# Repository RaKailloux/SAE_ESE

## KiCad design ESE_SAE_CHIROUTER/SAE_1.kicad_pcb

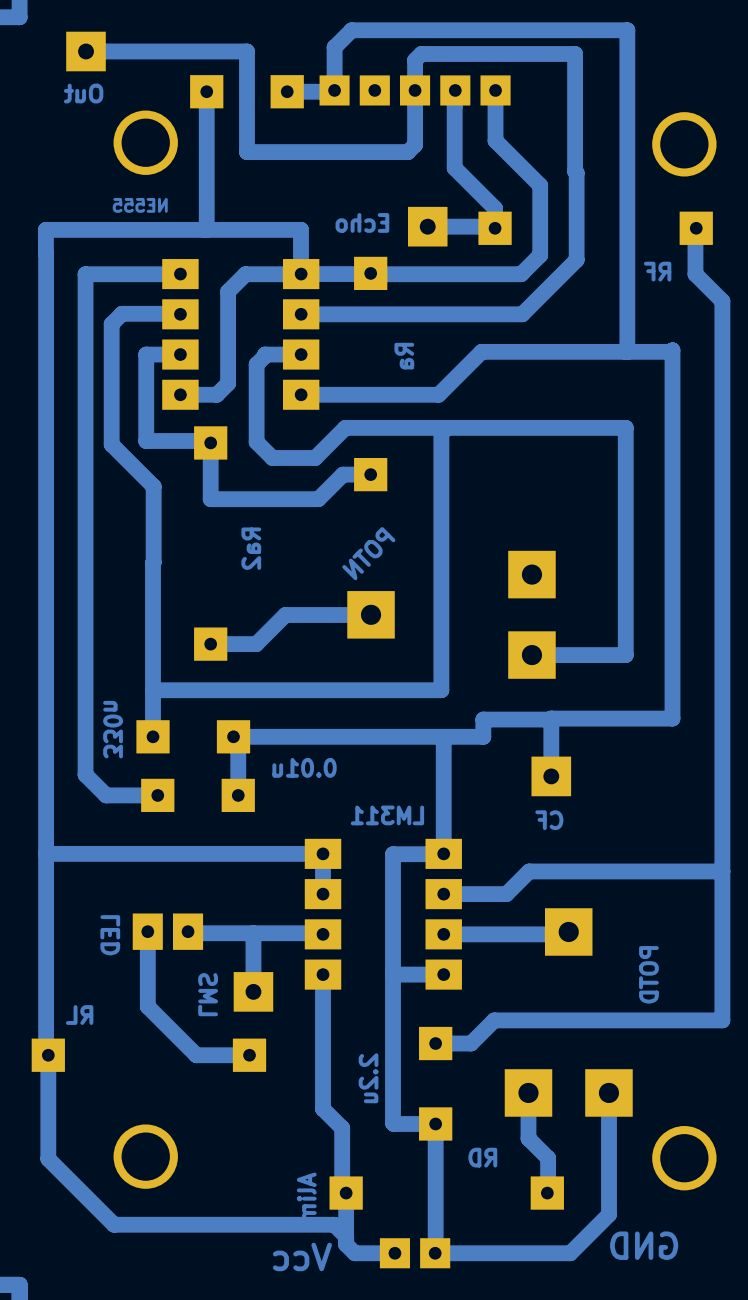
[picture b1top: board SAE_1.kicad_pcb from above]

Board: 2 copper layers, 24 parts (0 on the bottom side), 13 nets.

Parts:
1PIN, 1PIN#3, 1PIN#4: P***; 1pin
1PIN#2: 1pin
C1: 330nF; C2
C2, C5: 220nF; C2
C3: 0.01u; C2
D1: LED; LEDV
P1: CONN_2; PIN_ARRAY_2X1
P2: CONN_5; PIN_ARRAY_5x1
P3, P4, P5, P6: CONN_1; PINTST
POT1: POT; RV2X4
R1, R5: 12k; R5
R2: 8.2k; R5
R3: 82k; R5
R4: 150; R5
RV2: POT; RV2X4
U1: NE555; DIP-8__300
U2: LM311N; DIP-8__300

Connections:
+5V: C5.1, P1.2, P2.5, R1.2, R3.1, R4.1, U1.4, U1.8, U2.5, U2.6, U2.8
GND: C1.2, C2.2, C3.1, C5.2, P1.1, P2.1, P3.1, RV2.3, U1.1, U2.1, U2.4
unnamed: D1.1, R4.2
unnamed: D1.2, P4.1, U2.7
unnamed: C3.2, U1.5
unnamed: POT1.2, R5.2
unnamed: C1.1, POT1.1, U1.2, U1.6
unnamed: R1.1, R5.1, U1.7
unnamed: P2.3, P6.1, U1.3
unnamed: P2.4, P5.1, R2.1
unnamed: RV2.2, U2.2
unnamed: C2.1, R2.2, U2.3
unnamed: R3.2, RV2.1

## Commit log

2023-06-09 Programme
